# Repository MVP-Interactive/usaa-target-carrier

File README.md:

# 9dof sensor/light package with PoE

## About
Connect an ESP32-POE-ISO to a lsm9ds1 sensor via StemmaQT and a WS2811
light strand along with 12V power.

Because of the 12V power for the LEDs, the PoE on the ESP32-POE will not be used.

## Connections

Attach the Adafruit LSM9D1 Stemma power to the small 4 pin connector.

Connect the USB cable to the Olimex ESP32 board.

Connect the 10 pin ribbon cable to the Olimex ESP32 board.

Connect the LEDs to the 3 pin LED connector.

Connect the PoE extractor's ethernet out to the Olimex ESP32 board.

Connect the PoE extractor's 12v barrel to the 12v barrel on the board.

If using debug/programming USB-C board, not that while you can
physically plug the USB-C in other direction, only one direction will
work due to a flay in the board.

## Software

To build the software, use Arduino IDE 2.2.x.

Add the following board manager URLs in Preferences:
https://adafruit.github.io/arduino-board-index/package_adafruit_index.json
https://espressif.github.io/arduino-esp32/package_esp32_index.json

After that then press Ctrl+Shift+B to bring up the board manager dialog.
In the search box, type "esp32" and look for "esp32 by Expressif Systems" and click Install.

Add the following libraries in the Library Manager:
Arduino_LSM9DS1
Ethernet
Adafruit 9DOF
Adafruit BusIO
Adafruit NeoPixel
Adafruit Unified Sensor
ArduinoJson
CRC
CircularBuffer
HttpClient

If during the process, additional libraries are recommended, accept them.

## BOM
https://www.adafruit.com/product/4634
https://www.adafruit.com/product/4210
https://www.olimex.com/Products/IoT/ESP32/ESP32-POE-ISO/open-source-hardware

https://www.amazon.com/gp/product/B01AG923EU/

https://www.amazon.com/gp/product/B07L7QDZJW/

https://www.amazon.com/dp/B01DC0KIT2

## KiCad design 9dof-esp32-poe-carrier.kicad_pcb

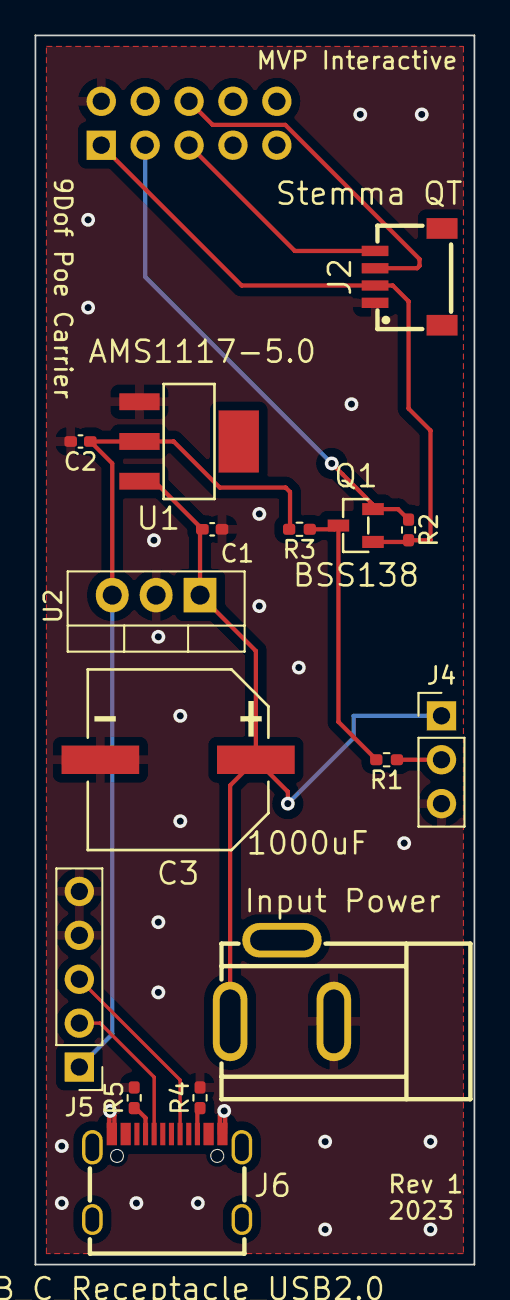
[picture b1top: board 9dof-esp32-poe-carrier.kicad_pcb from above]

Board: 2 copper layers, 25.4 x 71.1 mm, 17 parts (1 on the bottom side), 13 nets.

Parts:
C1, C2: 10uF; C_0402_1005Metric_Pad0.74x0.62mm_HandSolder
C3: 1000uF; CAP-SMD_BD10.0-L10.3-W10.3-FD
J1: Input Power; DC-IN-TH_DC005-T
J2: Stemma QT; CONN-SMD_4P-P1.00_SM04B-SRSS-TB-LF-SN
J3: UEXT_Slave; UEXT_SLAVE_BACKSIDE
J4: WS2811_strand; PinHeader_1x03_P2.54mm_Vertical
J5: USB to ESP32; PinHeader_1x05_P2.54mm_Vertical
J6: USB_C_Receptacle_USB2.0; USB-C_SMD-TYPE-C-31-M-12
Q1: BSS138; SOT-23-3_L2.9-W1.3-P1.90-LS2.4-BR
R1: 470; R_0402_1005Metric_Pad0.72x0.64mm_HandSolder
R2, R3: 10K; R_0402_1005Metric_Pad0.72x0.64mm_HandSolder
R4, R5: 5.1k; R_0402_1005Metric_Pad0.72x0.64mm_HandSolder
U1: AMS1117-5.0; SOT-223-3_L6.7-W3.7-P2.30-LS7.0-BR
U2: STM L7805CV; TO-220-3_Vertical

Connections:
+3V3: J2.2 (V+), J3.1 (3V3), Q1.1 (G), R2.2
+5V: C2.1, J5.1 (VBUS), R3.2, U1.2 (VO), U2.3 (VO)
+12V: C1.1, C3.1, J1.1 (In), J4.1, U1.3 (VI), U2.1 (VI)
D+: J5.3 (D+), J6.A6 (D+), J6.B6 (D+)
D-: J5.2 (D-), J6.A7 (D-), J6.B7 (D-)
DINv5: Q1.3 (D), R1.2, R3.1
DO3v3: J3.3 (TXD), Q1.2 (S), R2.1
GND: C1.2, C2.2, C3.2, J1.2 (Ext), J2.1 (GND), J3.2 (GND), J4.3, J5.4 (GND), J5.5 (Shield), J6.A1 (GND), J6.A12 (GND), J6.B1 (GND), J6.B12 (GND), R4.2, R5.2, U1.1 (GND), U2.2 (GND)
unnamed: J4.2, R1.1
unnamed: J6.A5 (CC1), R5.1
unnamed: J6.B5 (CC2), R4.1
SCL: J2.4 (SCL), J3.5 (SCL)
SDA: J2.3 (SDA), J3.6 (SDA)

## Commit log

2023-09-02 Import datasheets and .gitignore.
2023-09-02 Import initial components.
2023-09-02 Add readme.
2023-09-02 Add some parts notes.
2023-09-09 update with a bunch of parts extracted from EasyEDA. Change 1000uf cap.
2023-09-09 Updated redone schematic.
2023-09-10 Fiddle with parts, add via stiching, add silkscreen labels.
2023-09-10 Add rev_1 production files.
2023-09-23 Move project to subdir for organization sake.
2023-09-23 Add pinolut comment.
2023-09-26 Add some test programs.
2023-09-26 Add http client test.
2023-09-26 Move network setup in test to seperate function.
2023-09-26 Initial target code.
2023-09-26 Change watchdog timeout to not fail when http fails.
2023-09-26 LED fixes. Set IP automatically.
2023-09-27 Fix the LED split, flip colors, add disconnected state to LEDs.
2023-09-27 Fix URLS.
    Reorder headers. Speed up sample checking.
2023-09-27 reduce white brightness.
2023-09-27 Start collecting sample history.
2023-09-27 Change post to put.
2023-09-27 Updated URLs from Roman.
2023-09-27 Switch to vector magnatudes for hit detection.
2023-09-27 Add tag, tweak debug sensor threshold, add comments.
2023-09-27 REv 2.
2023-09-28 Add status/config API usage.
2023-09-28 Minor config corrections.
2023-09-28 Check for config keys before reading them.
2023-09-28 Mute hit bounces.
2023-09-28 Change hashing of mac to IP.
2023-09-28 Dump config URL as well on startup.
2023-09-28 Dump config payload if config isn't parsed as expected.
2023-09-28 Fix config parseing. Fix config using wrong URL, change hitWait.
2023-09-28 Add flashing on hits.
2023-09-30 Add status headers.
2023-10-01 Seperate the quiet period between hits and how long the strobing lasts.
2023-10-01 White space, comments.
2023-10-02 Work on config API to be more flexible.
2023-10-02 Update directions in README.
2023-10-02 Add white_level and blink_interval to config. Fix parseing ints in config.
2023-10-05 Update documentation for building software.
2023-10-05 Update README.md
    Add missing steps for board support in IDE.
2023-10-11 Slow LEDs on startup. Lower defaul white level. Add rev to status. Do a status/config cycle before any LEDs.
2023-10-11 Reset reasons now strings, also bump rev.
2023-10-11 increase LED startup speed.
2023-10-12 Add missed file.
2024-09-04 Add missing leds.h, update api url
2024-09-17 Fix warning
2024-09-17 Remove task wdt
2024-09-17 Refactor and update default values
2024-09-17 Reformat serial output logs
2024-09-17 Bump revision number
2024-10-28 Remove circle buffer
2024-10-28 Update threshold condition checks
2024-10-28 Increase hit wait time
2024-10-30 Calibrate accelerometer vector and compare against its deltas to trigger hits
